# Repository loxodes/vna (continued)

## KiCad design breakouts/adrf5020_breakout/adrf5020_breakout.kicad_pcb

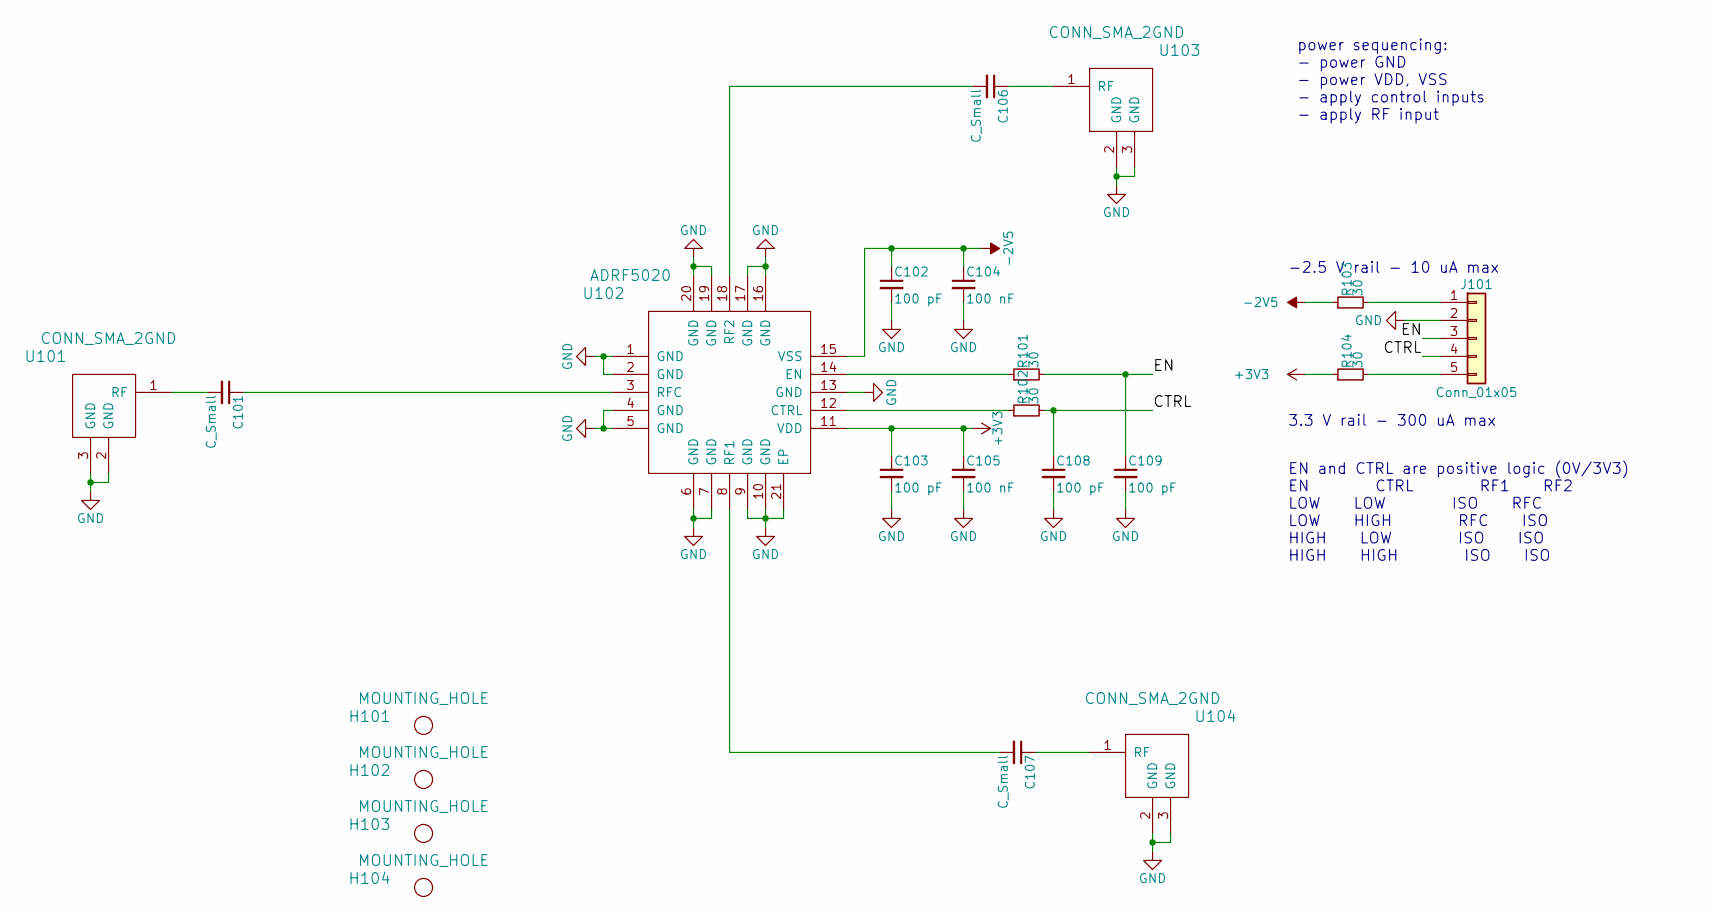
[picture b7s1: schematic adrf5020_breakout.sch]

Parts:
C101, C106, C107: C_Small; C_0402
C102, C103, C108, C109: 100 pF; C_0402
C104, C105: 100 nF; C_0402
H101, H102, H103, H104: MOUNTING_HOLE; MountingHole_2-7mm
J101: Conn_01x05; Pin_Header_Straight_1x05
R101, R102, R103, R104: 30; R_0402
U101, U103, U104: CONN_SMA_2GND; SMA_901-10512_6p7MIL_FR408_CPW_LAUNCH
U102: ADRF5020; ADRF5020BCCZN

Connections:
+3V3: C103.1, C105.1, R104.1, U102.11 (VDD)
-2V5: C102.1, C104.1, R103.1, U102.15 (VSS)
/CTRL: C108.1, J101.4, R102.2
/EN: C109.1, J101.3, R101.2
GND: C102.2, C103.2, C104.2, C105.2, C108.2, C109.2, J101.2, U101.2 (GND), U101.3 (GND), U102.1 (GND), U102.2 (GND), U102.4 (GND), U102.5 (GND), U102.6 (GND), U102.7 (GND), U102.9 (GND), U102.10 (GND), U102.13 (GND), U102.16 (GND), U102.17 (GND), U102.19 (GND), U102.20 (GND), U102.21 (EP), U103.2 (GND), U103.3 (GND), U104.2 (GND), U104.3 (GND)
unnamed: C101.1, U102.3 (RFC)
unnamed: C101.2, U101.1 (RF)
unnamed: C106.1, U103.1 (RF)
unnamed: C106.2, U102.18 (RF2)
unnamed: C107.1, U104.1 (RF)
unnamed: C107.2, U102.8 (RF1)
unnamed: J101.1, R103.2
unnamed: J101.5, R104.2
unnamed: R101.1, U102.14 (EN)
unnamed: R102.1, U102.12 (CTRL)

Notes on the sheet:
power sequencing: - power GND - power VDD, VSS - apply control inputs - apply RF input
-2.5 V rail - 10 uA max
3.3 V rail - 300 uA max
EN and CTRL are positive logic (0V/3V3) EN CTRL RF1 RF2 LOW LOW ISO RFC LOW HIGH RFC ISO HIGH LOW ISO ISO HIGH HIGH ISO ISO

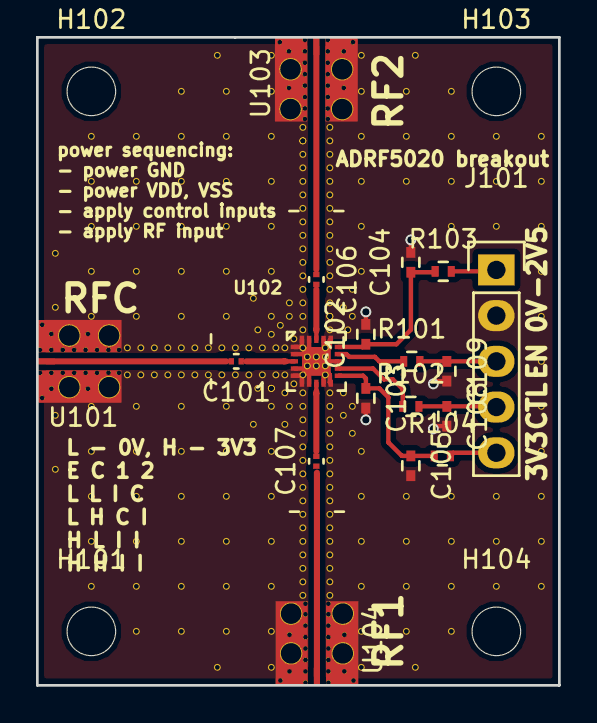
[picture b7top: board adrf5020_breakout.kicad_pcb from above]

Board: 4 copper layers, 29.0 x 36.0 mm, 22 parts (0 on the bottom side), 15 nets.
